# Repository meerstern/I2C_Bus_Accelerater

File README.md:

# I2Cバスアクセラレータ
I2C(Grove) adapter with a bus accelerater IC, LTC4311

## 概要 
  * 本基板は[LTC4311][1]を使用したI2C通信の信号波形を改善するバスアクセラレータです  
  * I2Cケーブルを延長する場合や多数デバイスを接続する場合に通信を安定させます  
  * 400pFのI2C仕様を大きく上回るバス負荷条件においてデータ伝送速度と信頼性を向上させます  
  * 最大400kHz動作です  
  * 電源範囲は1.6V～5.5Vです  
  * I2Cバスラインに挿入して使用します  
  * Grove互換コネクタを搭載しており、既存のデバイスに容易に接続できます  
  * 基板サイズ20mm x20mm、固定穴M3x4 幅15mm

## 注意
  * I2C信号によっては改善できない場合があります    
  * 本基板のGrove互換コネクタは2つとも共通です  
  * デバイス側/マイコン側の区別はないため、どちらに接続しても構いません 
  * I2Cハブ等で分岐して使用する場合は片側のみの接続でも構いません  
  * 本基板は目安として数m~10m程度までの延長に向いています  
  * 数10m以上延長する場合は高ドライブ電流バスバッファPCA9600D等が最適です  
   
## 販売サイト
  * [スイッチサイエンス][2] 

 [1]: https://www.analog.com/jp/products/ltc4311.html "*1"
 [2]: https://www.switch-science.com/products/7560

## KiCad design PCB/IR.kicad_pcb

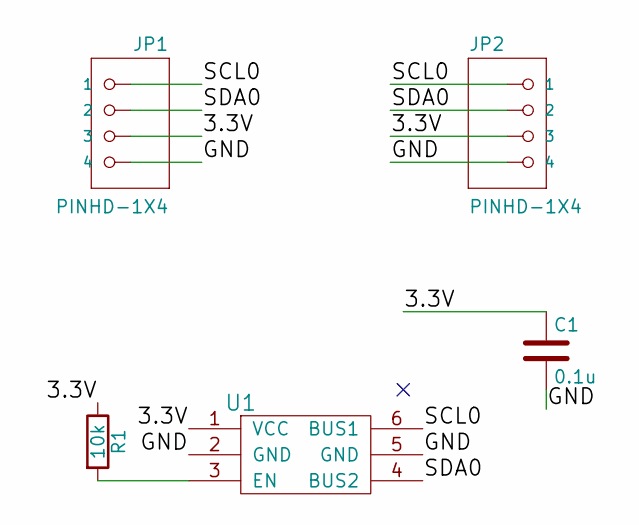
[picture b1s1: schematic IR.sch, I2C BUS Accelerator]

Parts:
C1: 0.1u; C-0603
JP1, JP2: PINHD-1X4; GROVE
R1: 10k; R-0603
U1: LTC4311; SC70-6L

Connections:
/3.3V: C1.1, JP1.3, JP2.3, R1.1, U1.1 (VCC)
/GND: C1.2, JP1.4, JP2.4, U1.2 (GND), U1.5 (GND)
/SCL0: JP1.1, JP2.1, U1.6 (BUS1)
/SDA0: JP1.2, JP2.2, U1.4 (BUS2)
unnamed: R1.2, U1.3 (EN)

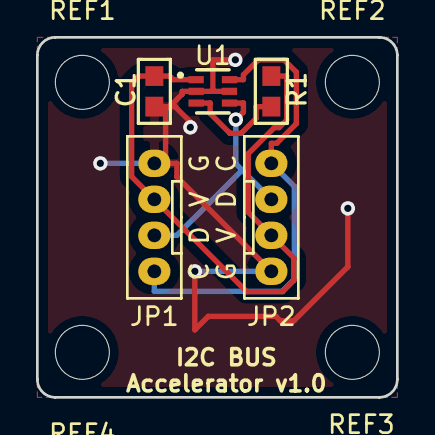
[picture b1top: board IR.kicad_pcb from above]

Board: 2 copper layers, 20.0 x 20.0 mm, 9 parts (0 on the bottom side), 5 nets.

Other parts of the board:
REF1, REF2, REF3, REF4: MountingHole_3mm

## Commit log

2021-09-13 Add README
2021-10-12 Add images
2021-10-12 Add pcb
